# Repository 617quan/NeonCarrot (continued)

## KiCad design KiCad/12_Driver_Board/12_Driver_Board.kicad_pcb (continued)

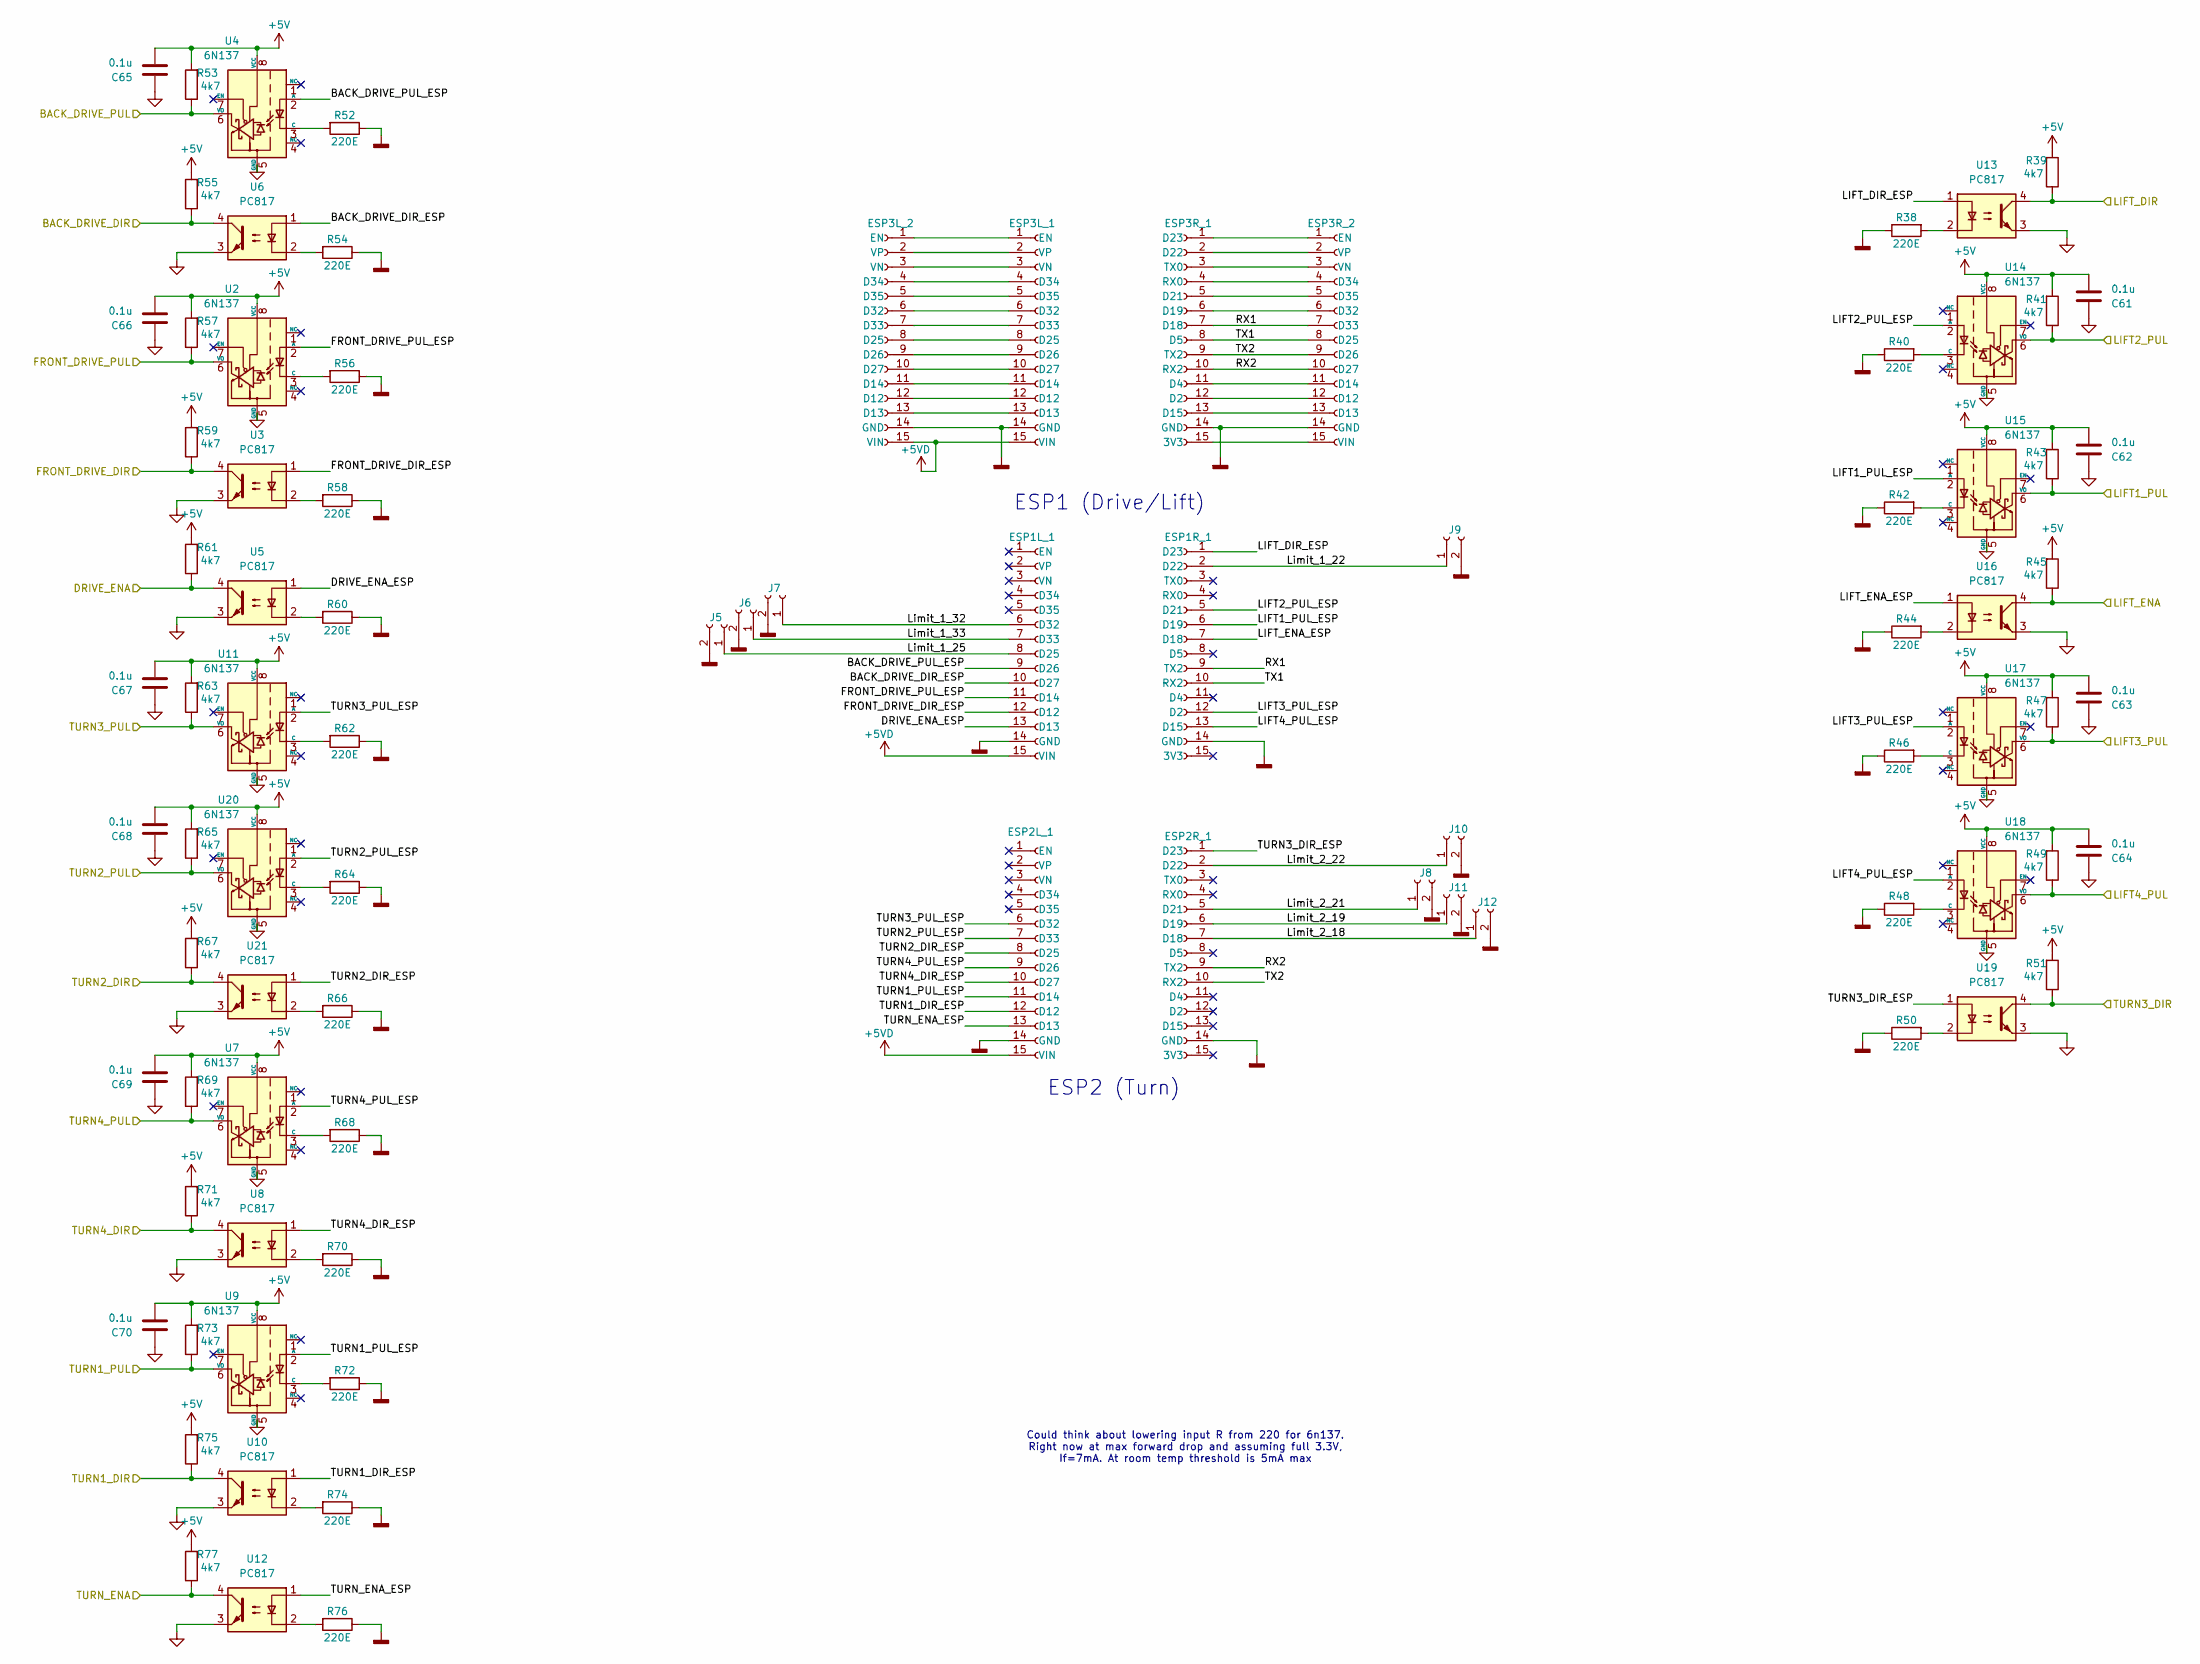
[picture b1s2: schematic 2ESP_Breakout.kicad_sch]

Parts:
C61, C62, C63, C64, C65, C66, C67, C68, C69, C70: 0.1u; C_0805_2012Metric
ESP1L_1, ESP1R_1, ESP2L_1, ESP2R_1, ESP3L_1, ESP3L_2, ESP3R_1, ESP3R_2: Conn_01x15_Socket; PinSocket_1x15_P2.54mm_Vertical
J5, J6, J7, J8, J9, J10, J11, J12: Conn_01x02_Socket; JST_PH_B2B-PH-K_1x02_P2.00mm_Vertical
R38, R40, R42, R44, R46, R48, R50, R52, R54, R56, R58, R60, R62, R64, R66, R68, R70, R72, R74, R76: 220E; R_0805_2012Metric
R39, R41, R43, R45, R47, R49, R51, R53, R55, R57, R59, R61, R63, R65, R67, R69, R71, R73, R75, R77: 4k7; R_0805_2012Metric
U2, U4, U7, U9, U11, U14, U15, U17, U18, U20: 6N137; DIP762W60P254L968H450Q8N
U3, U5, U6, U8, U10, U12, U13, U16, U19, U21: PC817; DIP-4_W7.62mm

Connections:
+5V: C61.1, C62.1, C63.1, C64.1, C65.1, C66.1, C67.1, C68.1, C69.1, C70.1, R39.2, R41.2, R43.2, R45.2, R47.2, R49.2, R51.2, R53.2, R55.2, R57.2, R59.2, R61.2, R63.2, R65.2, R67.2, R69.2, R71.2, R73.2, R75.2, R77.2, U2.8 (VCC), U4.8 (VCC), U7.8 (VCC), U9.8 (VCC), U11.8 (VCC), U14.8 (VCC), U15.8 (VCC), U17.8 (VCC), U18.8 (VCC), U20.8 (VCC); also elsewhere on the board
+5VD: ESP1L_1.15 (VIN), ESP2L_1.15 (VIN), ESP3L_1.15 (VIN), ESP3L_2.15 (VIN)
/BACK_DRIVE_DIR: R55.1, U6.4; also elsewhere on the board
/BACK_DRIVE_PUL: R53.1, U4.6 (VO); also elsewhere on the board
/DRIVE_ENA: R61.1, U5.4; also elsewhere on the board
/ESPs/BACK_DRIVE_DIR_ESP: ESP1L_1.10 (D27), U6.1
/ESPs/BACK_DRIVE_PUL_ESP: ESP1L_1.9 (D26), U4.2 (A)
/ESPs/DRIVE_ENA_ESP: ESP1L_1.13 (D13), U5.1
/ESPs/FRONT_DRIVE_DIR_ESP: ESP1L_1.12 (D12), U3.1
/ESPs/FRONT_DRIVE_PUL_ESP: ESP1L_1.11 (D14), U2.2 (A)
/ESPs/LIFT1_PUL_ESP: ESP1R_1.6 (D19), U15.2 (A)
/ESPs/LIFT2_PUL_ESP: ESP1R_1.5 (D21), U14.2 (A)
/ESPs/LIFT3_PUL_ESP: ESP1R_1.12 (D2), U17.2 (A)
/ESPs/LIFT4_PUL_ESP: ESP1R_1.13 (D15), U18.2 (A)
/ESPs/LIFT_DIR_ESP: ESP1R_1.1 (D23), U13.1
/ESPs/LIFT_ENA_ESP: ESP1R_1.7 (D18), U16.1
/ESPs/Limit_1_22: ESP1R_1.2 (D22), J9.1
/ESPs/Limit_1_25: ESP1L_1.8 (D25), J5.1
/ESPs/Limit_1_32: ESP1L_1.6 (D32), J7.1
/ESPs/Limit_1_33: ESP1L_1.7 (D33), J6.1
/ESPs/Limit_2_18: ESP2R_1.7 (D18), J12.1
/ESPs/Limit_2_19: ESP2R_1.6 (D19), J11.1
/ESPs/Limit_2_21: ESP2R_1.5 (D21), J8.1
/ESPs/Limit_2_22: ESP2R_1.2 (D22), J10.1
/ESPs/RX1: ESP1R_1.9 (TX2), ESP3R_1.7 (D18), ESP3R_2.7 (D33)
/ESPs/RX2: ESP2R_1.9 (TX2), ESP3R_1.10 (RX2), ESP3R_2.10 (D27)
/ESPs/TURN1_DIR_ESP: ESP2L_1.12 (D12), U10.1
/ESPs/TURN1_PUL_ESP: ESP2L_1.11 (D14), U9.2 (A)
/ESPs/TURN2_DIR_ESP: ESP2L_1.8 (D25), U21.1
/ESPs/TURN2_PUL_ESP: ESP2L_1.7 (D33), U20.2 (A)
/ESPs/TURN3_DIR_ESP: ESP2R_1.1 (D23), U19.1
/ESPs/TURN3_PUL_ESP: ESP2L_1.6 (D32), U11.2 (A)
/ESPs/TURN4_DIR_ESP: ESP2L_1.10 (D27), U8.1
/ESPs/TURN4_PUL_ESP: ESP2L_1.9 (D26), U7.2 (A)
/ESPs/TURN_ENA_ESP: ESP2L_1.13 (D13), U12.1
/ESPs/TX1: ESP1R_1.10 (RX2), ESP3R_1.8 (D5), ESP3R_2.8 (D25)
/ESPs/TX2: ESP2R_1.10 (RX2), ESP3R_1.9 (TX2), ESP3R_2.9 (D26)
/FRONT_DRIVE_DIR: R59.1, U3.4; also elsewhere on the board
/FRONT_DRIVE_PUL: R57.1, U2.6 (VO); also elsewhere on the board
/LIFT1_PUL: R43.1, U15.6 (VO); also elsewhere on the board
/LIFT2_PUL: R41.1, U14.6 (VO); also elsewhere on the board
/LIFT3_PUL: R47.1, U17.6 (VO); also elsewhere on the board
/LIFT4_PUL: R49.1, U18.6 (VO); also elsewhere on the board
/LIFT_DIR: R39.1, U13.4; also elsewhere on the board
/LIFT_ENA: R45.1, U16.4; also elsewhere on the board
/TURN1_DIR: R75.1, U10.4; also elsewhere on the board
/TURN1_PUL: R73.1, U9.6 (VO); also elsewhere on the board
/TURN2_DIR: R67.1, U21.4; also elsewhere on the board
/TURN2_PUL: R65.1, U20.6 (VO); also elsewhere on the board
/TURN3_DIR: R51.1, U19.4; also elsewhere on the board
/TURN3_PUL: R63.1, U11.6 (VO); also elsewhere on the board
/TURN4_DIR: R71.1, U8.4; also elsewhere on the board
/TURN4_PUL: R69.1, U7.6 (VO); also elsewhere on the board
/TURN_ENA: R77.1, U12.4; also elsewhere on the board
GND: C61.2, C62.2, C63.2, C64.2, C65.2, C66.2, C67.2, C68.2, C69.2, C70.2, U2.5 (GND), U3.3, U4.5 (GND), U5.3, U6.3, U7.5 (GND), U8.3, U9.5 (GND), U10.3, U11.5 (GND), U12.3, U13.3, U14.5 (GND), U15.5 (GND), U16.3, U17.5 (GND), U18.5 (GND), U19.3, U20.5 (GND), U21.3; also elsewhere on the board
GNDD: ESP1L_1.14 (GND), ESP1R_1.14 (GND), ESP2L_1.14 (GND), ESP2R_1.14 (GND), ESP3L_1.14 (GND), ESP3L_2.14 (GND), ESP3R_1.14 (GND), ESP3R_2.14 (GND), J5.2, J6.2, J7.2, J8.2, J9.2, J10.2, J11.2, J12.2, R38.1, R40.1, R42.1, R44.1, R46.1, R48.1, R50.1, R52.1, R54.1, R56.1, R58.1, R60.1, R62.1, R64.1, R66.1, R68.1, R70.1, R72.1, R74.1, R76.1
unnamed: ESP3L_1.12 (D12), ESP3L_2.12 (D12)
unnamed: ESP3L_1.13 (D13), ESP3L_2.13 (D13)
unnamed: ESP3L_1.11 (D14), ESP3L_2.11 (D14)
unnamed: ESP3L_1.8 (D25), ESP3L_2.8 (D25)
unnamed: ESP3L_1.9 (D26), ESP3L_2.9 (D26)
unnamed: ESP3L_1.10 (D27), ESP3L_2.10 (D27)
unnamed: ESP3L_1.6 (D32), ESP3L_2.6 (D32)
unnamed: ESP3L_1.7 (D33), ESP3L_2.7 (D33)
unnamed: ESP3L_1.4 (D34), ESP3L_2.4 (D34)
unnamed: ESP3L_1.5 (D35), ESP3L_2.5 (D35)
unnamed: ESP3L_1.1 (EN), ESP3L_2.1 (EN)
unnamed: ESP3L_1.3 (VN), ESP3L_2.3 (VN)
unnamed: ESP3L_1.2 (VP), ESP3L_2.2 (VP)
unnamed: ESP3R_1.15 (3V3), ESP3R_2.15 (VIN)
unnamed: ESP3R_1.12 (D2), ESP3R_2.12 (D12)
unnamed: ESP3R_1.11 (D4), ESP3R_2.11 (D14)
unnamed: ESP3R_1.13 (D15), ESP3R_2.13 (D13)
unnamed: ESP3R_1.6 (D19), ESP3R_2.6 (D32)
unnamed: ESP3R_1.5 (D21), ESP3R_2.5 (D35)
unnamed: ESP3R_1.2 (D22), ESP3R_2.2 (VP)
unnamed: ESP3R_1.1 (D23), ESP3R_2.1 (EN)
unnamed: ESP3R_1.4 (RX0), ESP3R_2.4 (D34)
unnamed: ESP3R_1.3 (TX0), ESP3R_2.3 (VN)
unnamed: R38.2, U13.2
unnamed: R44.2, U16.2
unnamed: R50.2, U19.2
unnamed: R54.2, U6.2
unnamed: R58.2, U3.2
unnamed: R60.2, U5.2
unnamed: R66.2, U21.2
unnamed: R70.2, U8.2
unnamed: R74.2, U10.2
unnamed: R76.2, U12.2
unnamed: R56.2, U2.3 (C)
unnamed: R52.2, U4.3 (C)
unnamed: R68.2, U7.3 (C)
unnamed: R72.2, U9.3 (C)
unnamed: R62.2, U11.3 (C)
unnamed: R40.2, U14.3 (C)
unnamed: R42.2, U15.3 (C)
unnamed: R46.2, U17.3 (C)
unnamed: R48.2, U18.3 (C)
unnamed: R64.2, U20.3 (C)

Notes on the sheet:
ESP2 (Turn)
Could think about lowering input R from 220 for 6n137. Right now at max forward drop and assuming full 3.3V, If=7mA. At room temp threshold is 5mA max
ESP1 (Drive/Lift)

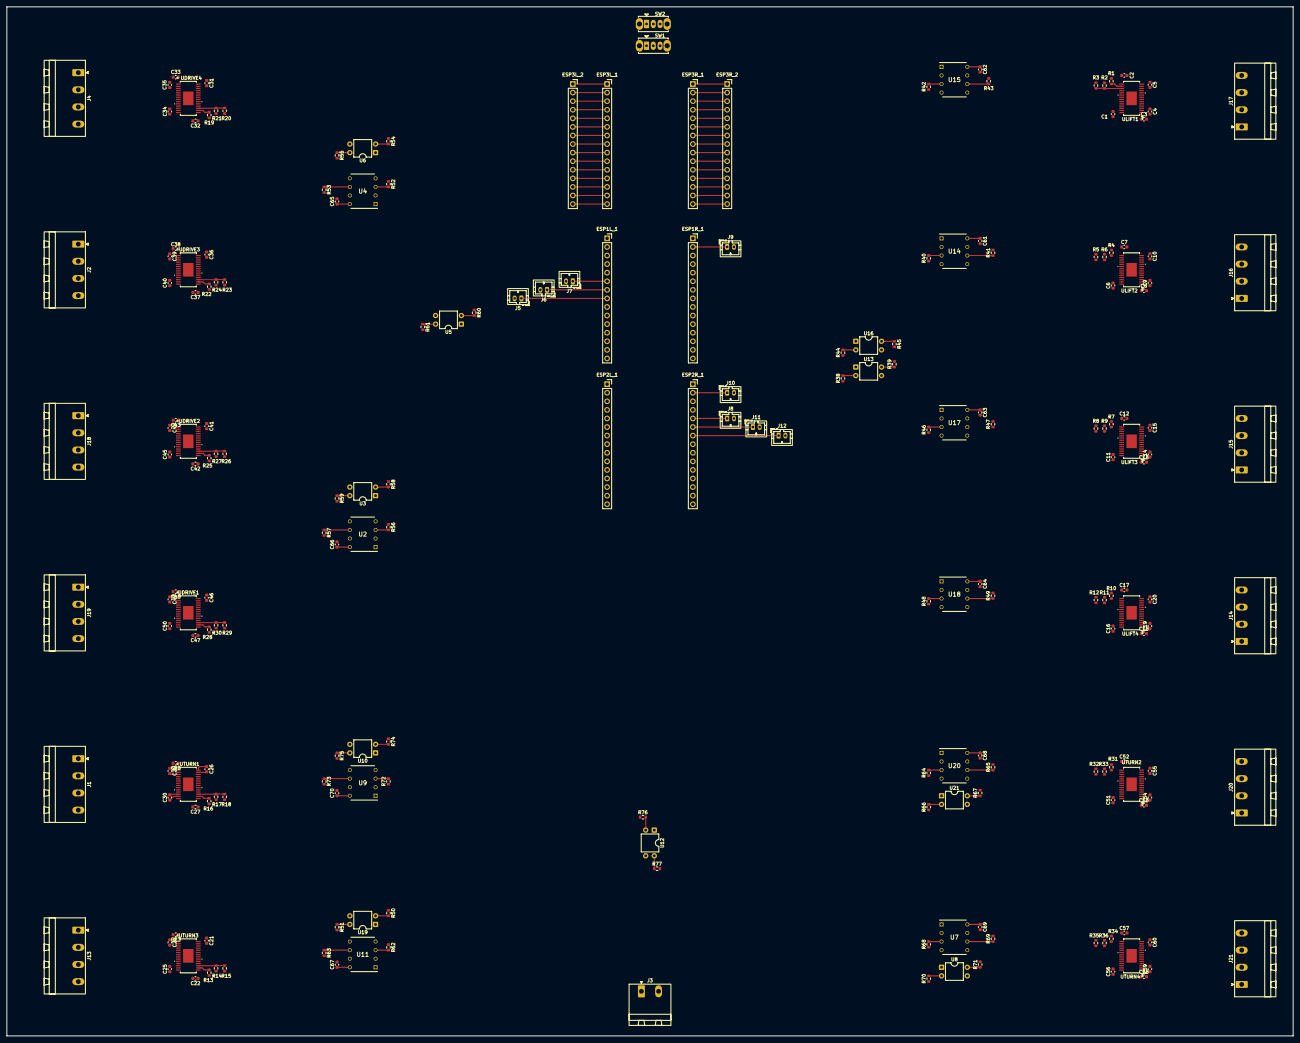
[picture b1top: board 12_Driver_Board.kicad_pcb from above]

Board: 4 copper layers, 381.0 x 304.8 mm, 209 parts (0 on the bottom side), 222 nets.

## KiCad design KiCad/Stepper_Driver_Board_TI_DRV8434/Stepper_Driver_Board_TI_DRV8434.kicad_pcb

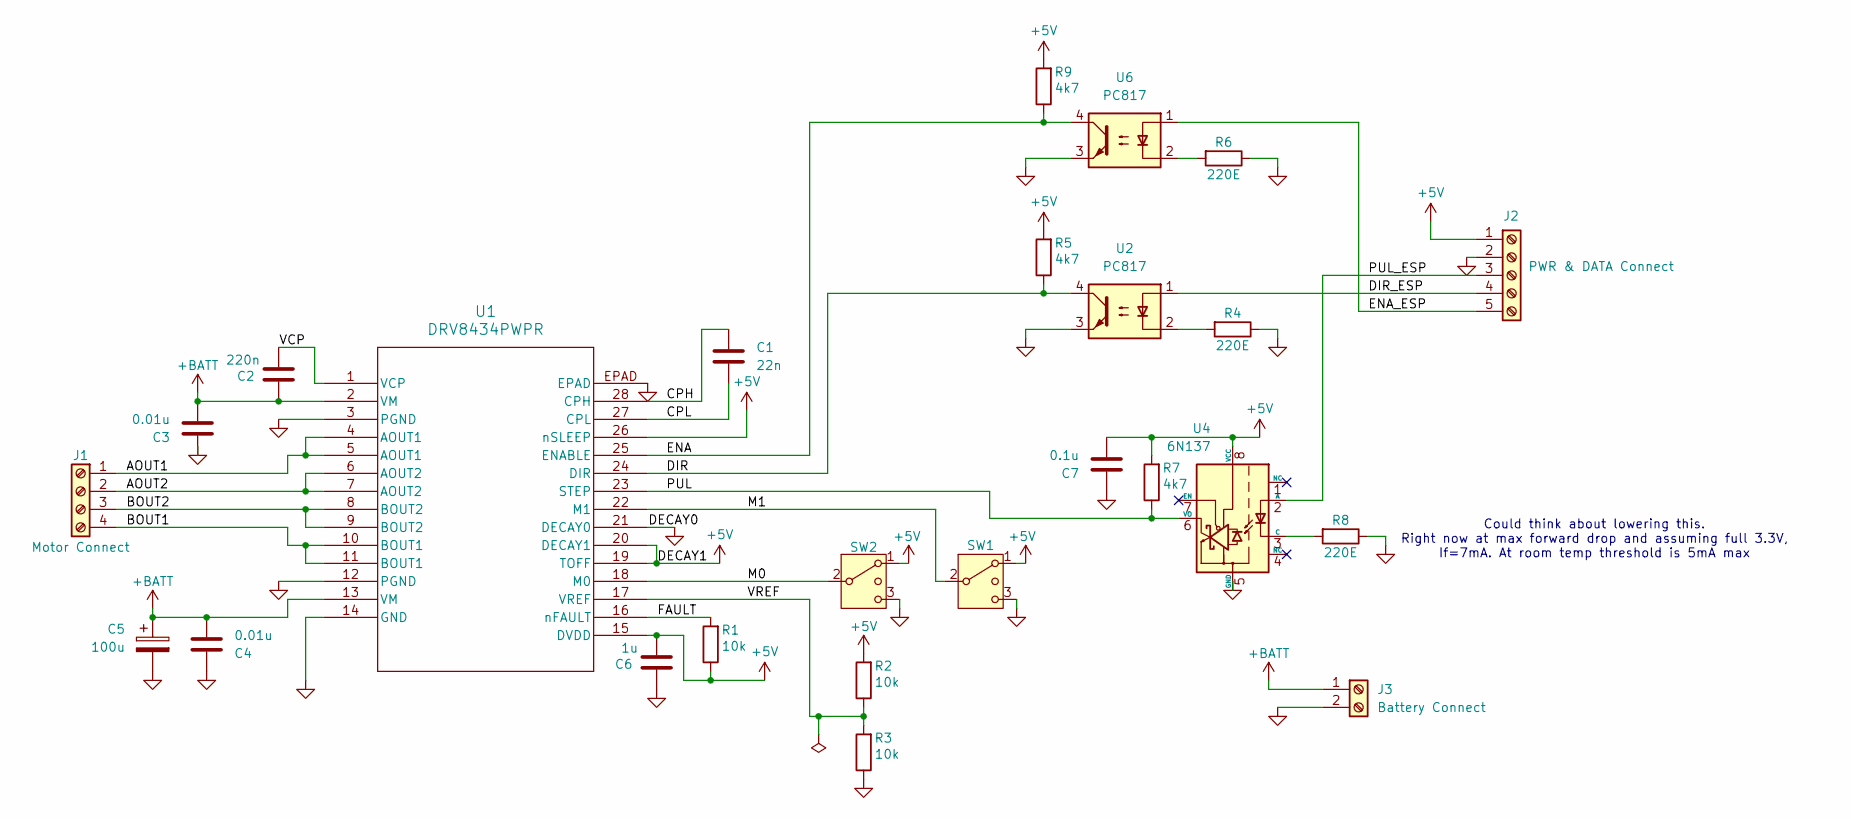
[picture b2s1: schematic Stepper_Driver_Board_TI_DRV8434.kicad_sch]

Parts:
C1: 22n; C_0603_1608Metric_Pad1.08x0.95mm_HandSolder
C2: 220n; C_0603_1608Metric_Pad1.08x0.95mm_HandSolder
C3, C4: 0.01u; C_0603_1608Metric_Pad1.08x0.95mm_HandSolder
C5: 100u; CP_Radial_D8.0mm_P3.50mm
C6: 1u; C_0603_1608Metric_Pad1.08x0.95mm_HandSolder
C7: 0.1u; C_0603_1608Metric_Pad1.08x0.95mm_HandSolder
J1: Motor Connect; PhoenixContact_MSTBA_2,5_4-G-5,08_1x04_P5.08mm_Horizontal
J2: PWR & DATA Connect; PhoenixContact_MSTBA_2,5_5-G-5,08_1x05_P5.08mm_Horizontal
J3: Battery Connect; PhoenixContact_MSTBA_2,5_2-G-5,08_1x02_P5.08mm_Horizontal
R1, R2, R3: 10k; R_0603_1608Metric_Pad0.98x0.95mm_HandSolder
R4, R6, R8: 220E; R_0603_1608Metric_Pad0.98x0.95mm_HandSolder
R5, R7, R9: 4k7; R_0603_1608Metric_Pad0.98x0.95mm_HandSolder
SW1, SW2: SW_SPDT_MSM; SW_Slide_SPDT_Straight_CK_OS102011MS2Q
U1: DRV8434PWPR; TSSOP_34PWPR_TEX
U2, U6: PC817; DIP-4_W7.62mm
U4: 6N137; DIP762W60P254L968H450Q8N

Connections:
+5V: C6.1, C7.1, J2.1, R1.1, R2.2, R5.2, R7.2, R9.2, SW1.1, SW2.1, U1.15 (DVDD), U1.19 (TOFF), U1.20 (DECAY1), U1.26 (nSLEEP), U4.8 (VCC)
+BATT: C2.2, C3.1, C4.1, C5.1, J3.1, U1.2 (VM), U1.13 (VM)
/AOUT1: J1.1, U1.4 (AOUT1), U1.5 (AOUT1)
/AOUT2: J1.2, U1.6 (AOUT2), U1.7 (AOUT2)
/BOUT1: J1.4, U1.10 (BOUT1), U1.11 (BOUT1)
/BOUT2: J1.3, U1.8 (BOUT2), U1.9 (BOUT2)
/CPH: C1.1, U1.28 (CPH)
/CPL: C1.2, U1.27 (CPL)
/DIR: R5.1, U1.24 (DIR), U2.4
/DIR_ESP: J2.4, U2.1
/ENA: R9.1, U1.25 (ENABLE), U6.4
/ENA_ESP: J2.5, U6.1
/FAULT: R1.2, U1.16 (nFAULT)
/M0: SW2.2 (3), U1.18 (M0)
/M1: SW1.2 (3), U1.22 (M1)
/PUL: R7.1, U1.23 (STEP), U4.6 (VO)
/PUL_ESP: J2.3, U4.2 (A)
/VCP: C2.1, U1.1 (VCP)
/VREF: R2.1, R3.2, U1.17 (VREF)
GND: C3.2, C4.2, C5.2, C6.2, C7.2, J2.2, J3.2, R3.1, R4.1, R6.1, R8.1, SW1.3 (4), SW2.3 (4), U1.3 (PGND), U1.12 (PGND), U1.14 (GND), U1.21 (DECAY0), U1.EPAD, U2.3, U4.5 (GND), U6.3
unnamed: R4.2, U2.2
unnamed: R6.2, U6.2
unnamed: R8.2, U4.3 (C)

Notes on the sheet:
Could think about lowering this. Right now at max forward drop and assuming full 3.3V, If=7mA. At room temp threshold is 5mA max

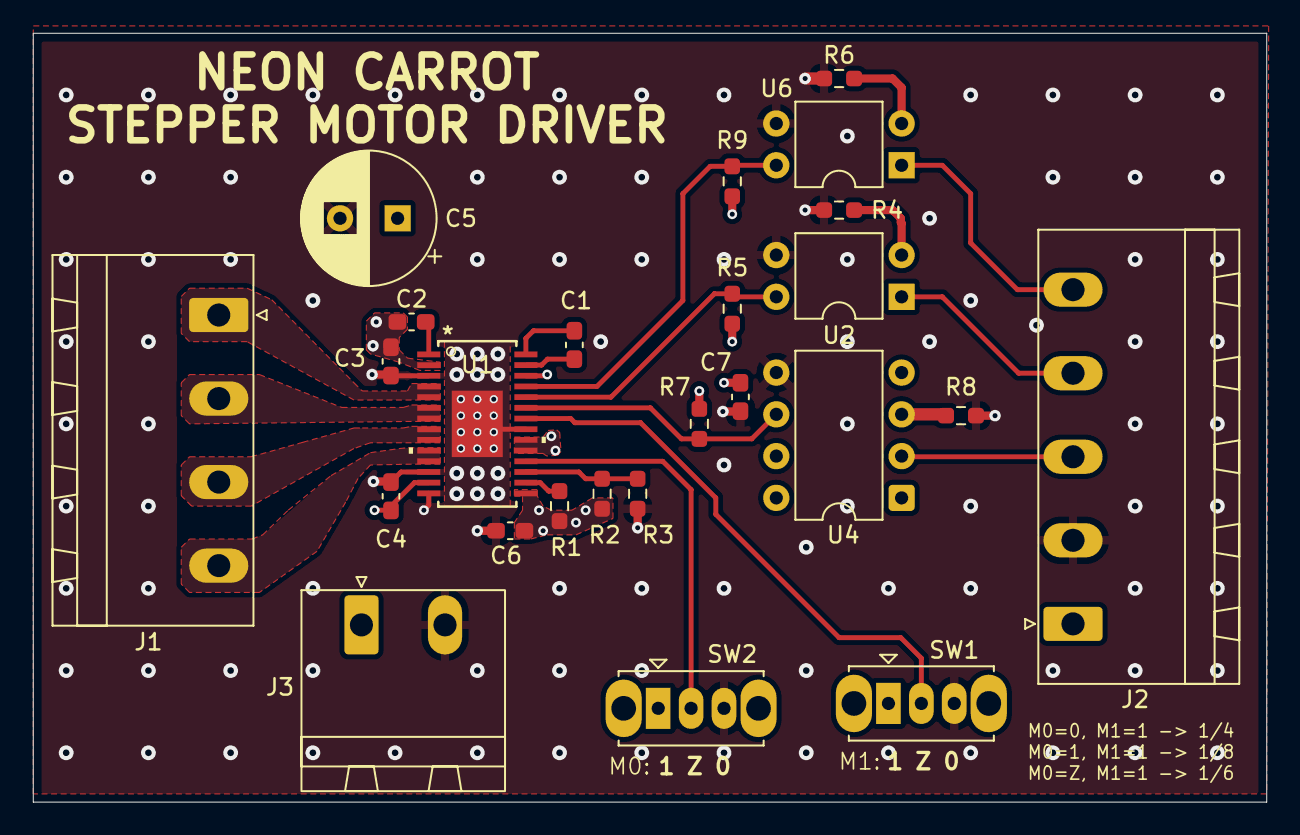
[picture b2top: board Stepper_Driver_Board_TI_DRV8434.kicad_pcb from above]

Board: 4 copper layers, 75.0 x 46.8 mm, 25 parts (0 on the bottom side), 23 nets.

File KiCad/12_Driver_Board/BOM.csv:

"Reference","Value","Datasheet","Footprint","Qty","DNP"
"C1","22n","~","Capacitor_SMD:C_0603_1608Metric_Pad1.08x0.95mm_HandSolder","1",""
"C2","220n","~","Capacitor_SMD:C_0603_1608Metric_Pad1.08x0.95mm_HandSolder","1",""
"C3,C4","0.01u","~","Capacitor_SMD:C_0603_1608Metric_Pad1.08x0.95mm_HandSolder","2",""
"C5","100u","~","","1",""
"C6","1u","~","Capacitor_SMD:C_0603_1608Metric_Pad1.08x0.95mm_HandSolder","1",""
"C7","0.1u","~","Capacitor_SMD:C_0603_1608Metric_Pad1.08x0.95mm_HandSolder","1",""
"J1","Motor Connect","~","Connector_Phoenix_MSTB:PhoenixContact_MSTBA_2,5_4-G-5,08_1x04_P5.08mm_Horizontal","1",""
"J2","PWR & DATA Connect","~","Connector_Phoenix_MSTB:PhoenixContact_MSTBA_2,5_5-G-5,08_1x05_P5.08mm_Horizontal","1",""
"R1,R2,R3","10k","~","Resistor_SMD:R_0603_1608Metric_Pad0.98x0.95mm_HandSolder","3",""
"R4,R6,R8","220E","~","Resistor_SMD:R_0603_1608Metric_Pad0.98x0.95mm_HandSolder","3",""
"R5,R7,R9","4k7","~","Resistor_SMD:R_0603_1608Metric_Pad0.98x0.95mm_HandSolder","3",""
"SW1,SW2","SW_SPDT_MSM","~","Button_Switch_THT:SW_Slide_SPDT_Straight_CK_OS102011MS2Q","2",""
"U1","DRV8434PWPR","https://www.ti.com/lit/gpn/drv8434","TSSOP_34PWPR_TEX","1",""
"U2,U6","PC817","http://www.soselectronic.cz/a_info/resource/d/pc817.pdf","Package_DIP:DIP-4_W7.62mm","2",""
"U4","6N137","https://docs.broadcom.com/docs/AV02-0940EN","Package_DIP:DIP-8_W7.62mm","1",""

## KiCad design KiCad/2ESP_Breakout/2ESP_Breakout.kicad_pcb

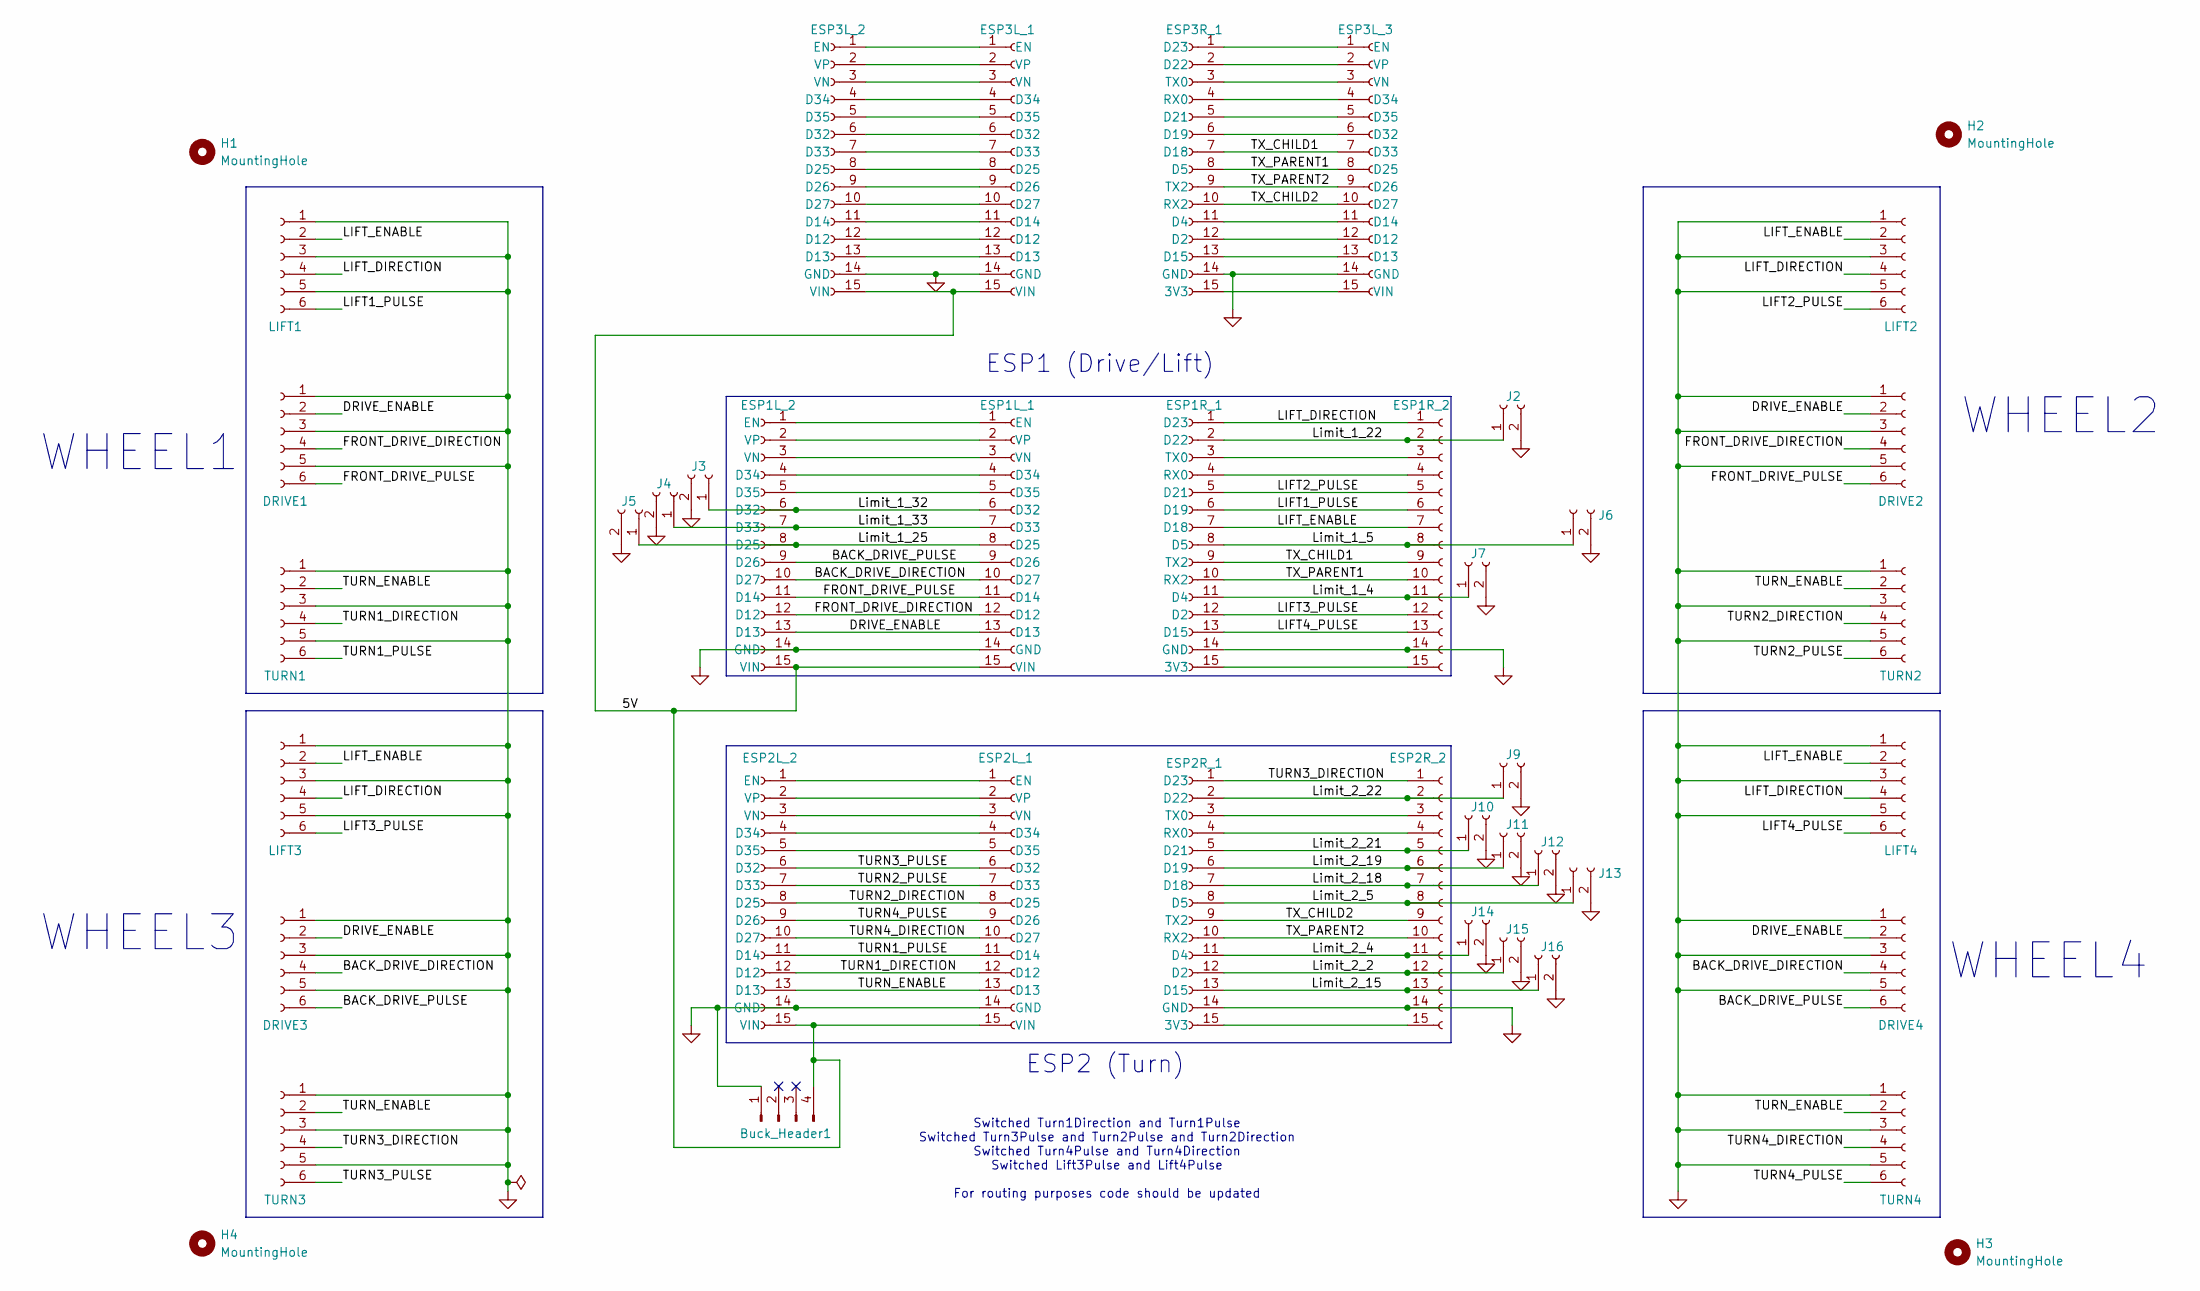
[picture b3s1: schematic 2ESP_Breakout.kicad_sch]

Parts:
Buck_Header1: Conn_01x04_Pin; PinHeader_1x04_P2.54mm_Vertical
DRIVE1, DRIVE2, DRIVE3, DRIVE4: Conn_01x06_Socket; JST_PH_B6B-PH-K_1x06_P2.00mm_Vertical
ESP1L_1, ESP1L_2, ESP1R_1, ESP1R_2, ESP2L_1, ESP2L_2, ESP2R_1, ESP2R_2, ESP3L_1, ESP3L_2, ESP3L_3, ESP3R_1: Conn_01x15_Socket; PinSocket_1x15_P2.54mm_Vertical
H1, H2, H3, H4: MountingHole; MountingHole_3.2mm_M3
J2, J3, J4, J5, J6, J7, J9, J10, J11, J12, J13, J14, J15, J16: Conn_01x02_Socket; JST_PH_B2B-PH-K_1x02_P2.00mm_Vertical
LIFT1, LIFT2, LIFT3, LIFT4: Conn_01x06_Socket; JST_PH_B6B-PH-K_1x06_P2.00mm_Vertical
TURN1, TURN2, TURN3, TURN4: Conn_01x06_Socket; JST_PH_B6B-PH-K_1x06_P2.00mm_Vertical

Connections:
/5V: Buck_Header1.4, ESP1L_1.15 (VIN), ESP1L_2.15 (VIN), ESP2L_1.15 (VIN), ESP2L_2.15 (VIN), ESP3L_1.15 (VIN), ESP3L_2.15 (VIN)
/BACK_DRIVE_DIRECTION: DRIVE3.4, DRIVE4.4, ESP1L_1.10 (D27), ESP1L_2.10 (D27)
/BACK_DRIVE_PULSE: DRIVE3.6, DRIVE4.6, ESP1L_1.9 (D26), ESP1L_2.9 (D26)
/DRIVE_ENABLE: DRIVE1.2, DRIVE2.2, DRIVE3.2, DRIVE4.2, ESP1L_1.13 (D13), ESP1L_2.13 (D13)
/FRONT_DRIVE_DIRECTION: DRIVE1.4, DRIVE2.4, ESP1L_1.12 (D12), ESP1L_2.12 (D12)
/FRONT_DRIVE_PULSE: DRIVE1.6, DRIVE2.6, ESP1L_1.11 (D14), ESP1L_2.11 (D14)
/LIFT1_PULSE: ESP1R_1.6 (D19), ESP1R_2.6 (D19), LIFT1.6
/LIFT2_PULSE: ESP1R_1.5 (D21), ESP1R_2.5 (D21), LIFT2.6
/LIFT3_PULSE: ESP1R_1.12 (D2), ESP1R_2.12 (D2), LIFT3.6
/LIFT4_PULSE: ESP1R_1.13 (D15), ESP1R_2.13 (D15), LIFT4.6
/LIFT_DIRECTION: ESP1R_1.1 (D23), ESP1R_2.1 (D23), LIFT1.4, LIFT2.4, LIFT3.4, LIFT4.4
/LIFT_ENABLE: ESP1R_1.7 (D18), ESP1R_2.7 (D18), LIFT1.2, LIFT2.2, LIFT3.2, LIFT4.2
/Limit_1_4: ESP1R_1.11 (D4), ESP1R_2.11 (D4), J7.1
/Limit_1_5: ESP1R_1.8 (D5), ESP1R_2.8 (D5), J6.1
/Limit_1_22: ESP1R_1.2 (D22), ESP1R_2.2 (D22), J2.1
/Limit_1_25: ESP1L_1.8 (D25), ESP1L_2.8 (D25), J5.1
/Limit_1_32: ESP1L_1.6 (D32), ESP1L_2.6 (D32), J3.1
/Limit_1_33: ESP1L_1.7 (D33), ESP1L_2.7 (D33), J4.1
/Limit_2_2: ESP2R_1.12 (D2), ESP2R_2.12 (D2), J15.1
/Limit_2_4: ESP2R_1.11 (D4), ESP2R_2.11 (D4), J14.1
/Limit_2_5: ESP2R_1.8 (D5), ESP2R_2.8 (D5), J13.1
/Limit_2_15: ESP2R_1.13 (D15), ESP2R_2.13 (D15), J16.1
/Limit_2_18: ESP2R_1.7 (D18), ESP2R_2.7 (D18), J12.1
/Limit_2_19: ESP2R_1.6 (D19), ESP2R_2.6 (D19), J11.1
/Limit_2_21: ESP2R_1.5 (D21), ESP2R_2.5 (D21), J10.1
/Limit_2_22: ESP2R_1.2 (D22), ESP2R_2.2 (D22), J9.1
/TURN1_DIRECTION: ESP2L_1.12 (D12), ESP2L_2.12 (D12), TURN1.4
/TURN1_PULSE: ESP2L_1.11 (D14), ESP2L_2.11 (D14), TURN1.6
/TURN2_DIRECTION: ESP2L_1.8 (D25), ESP2L_2.8 (D25), TURN2.4
/TURN2_PULSE: ESP2L_1.7 (D33), ESP2L_2.7 (D33), TURN2.6
/TURN3_DIRECTION: ESP2R_1.1 (D23), ESP2R_2.1 (D23), TURN3.4
/TURN3_PULSE: ESP2L_1.6 (D32), ESP2L_2.6 (D32), TURN3.6
/TURN4_DIRECTION: ESP2L_1.10 (D27), ESP2L_2.10 (D27), TURN4.4
/TURN4_PULSE: ESP2L_1.9 (D26), ESP2L_2.9 (D26), TURN4.6
/TURN_ENABLE: ESP2L_1.13 (D13), ESP2L_2.13 (D13), TURN1.2, TURN2.2, TURN3.2, TURN4.2
/TX_CHILD1: ESP1R_1.9 (TX2), ESP1R_2.9 (TX2), ESP3L_3.7 (D33), ESP3R_1.7 (D18)
/TX_CHILD2: ESP2R_1.9 (TX2), ESP2R_2.9 (TX2), ESP3L_3.10 (D27), ESP3R_1.10 (RX2)
/TX_PARENT1: ESP1R_1.10 (RX2), ESP1R_2.10 (RX2), ESP3L_3.8 (D25), ESP3R_1.8 (D5)
/TX_PARENT2: ESP2R_1.10 (RX2), ESP2R_2.10 (RX2), ESP3L_3.9 (D26), ESP3R_1.9 (TX2)
GND: Buck_Header1.1, DRIVE1.1, DRIVE1.3, DRIVE1.5, DRIVE2.1, DRIVE2.3, DRIVE2.5, DRIVE3.1, DRIVE3.3, DRIVE3.5, DRIVE4.1, DRIVE4.3, DRIVE4.5, ESP1L_1.14 (GND), ESP1L_2.14 (GND), ESP1R_1.14 (GND), ESP1R_2.14 (GND), ESP2L_1.14 (GND), ESP2L_2.14 (GND), ESP2R_1.14 (GND), ESP2R_2.14 (GND), ESP3L_1.14 (GND), ESP3L_2.14 (GND), ESP3L_3.14 (GND), ESP3R_1.14 (GND), J2.2, J3.2, J4.2, J5.2, J6.2, J7.2, J9.2, J10.2, J11.2, J12.2, J13.2, J14.2, J15.2, J16.2, LIFT1.1, LIFT1.3, LIFT1.5, LIFT2.1, LIFT2.3, LIFT2.5, LIFT3.1, LIFT3.3, LIFT3.5, LIFT4.1, LIFT4.3, LIFT4.5, TURN1.1, TURN1.3, TURN1.5, TURN2.1, TURN2.3, TURN2.5, TURN3.1, TURN3.3, TURN3.5, TURN4.1, TURN4.3, TURN4.5
unnamed: ESP1L_1.4 (D34), ESP1L_2.4 (D34)
unnamed: ESP1L_1.5 (D35), ESP1L_2.5 (D35)
unnamed: ESP1L_1.1 (EN), ESP1L_2.1 (EN)
unnamed: ESP1L_1.3 (VN), ESP1L_2.3 (VN)
unnamed: ESP1L_1.2 (VP), ESP1L_2.2 (VP)
unnamed: ESP1R_1.15 (3V3), ESP1R_2.15 (3V3)
unnamed: ESP1R_1.4 (RX0), ESP1R_2.4 (RX0)
unnamed: ESP1R_1.3 (TX0), ESP1R_2.3 (TX0)
unnamed: ESP2L_1.4 (D34), ESP2L_2.4 (D34)
unnamed: ESP2L_1.5 (D35), ESP2L_2.5 (D35)
unnamed: ESP2L_1.1 (EN), ESP2L_2.1 (EN)
unnamed: ESP2L_1.3 (VN), ESP2L_2.3 (VN)
unnamed: ESP2L_1.2 (VP), ESP2L_2.2 (VP)
unnamed: ESP2R_1.15 (3V3), ESP2R_2.15 (3V3)
unnamed: ESP2R_1.4 (RX0), ESP2R_2.4 (RX0)
unnamed: ESP2R_1.3 (TX0), ESP2R_2.3 (TX0)
unnamed: ESP3L_1.12 (D12), ESP3L_2.12 (D12)
unnamed: ESP3L_1.13 (D13), ESP3L_2.13 (D13)
unnamed: ESP3L_1.11 (D14), ESP3L_2.11 (D14)
unnamed: ESP3L_1.8 (D25), ESP3L_2.8 (D25)
unnamed: ESP3L_1.9 (D26), ESP3L_2.9 (D26)
unnamed: ESP3L_1.10 (D27), ESP3L_2.10 (D27)
unnamed: ESP3L_1.6 (D32), ESP3L_2.6 (D32)
unnamed: ESP3L_1.7 (D33), ESP3L_2.7 (D33)
unnamed: ESP3L_1.4 (D34), ESP3L_2.4 (D34)
unnamed: ESP3L_1.5 (D35), ESP3L_2.5 (D35)
unnamed: ESP3L_1.1 (EN), ESP3L_2.1 (EN)
unnamed: ESP3L_1.3 (VN), ESP3L_2.3 (VN)
unnamed: ESP3L_1.2 (VP), ESP3L_2.2 (VP)
unnamed: ESP3L_3.12 (D12), ESP3R_1.12 (D2)
unnamed: ESP3L_3.13 (D13), ESP3R_1.13 (D15)
unnamed: ESP3L_3.11 (D14), ESP3R_1.11 (D4)
unnamed: ESP3L_3.6 (D32), ESP3R_1.6 (D19)
unnamed: ESP3L_3.4 (D34), ESP3R_1.4 (RX0)
unnamed: ESP3L_3.5 (D35), ESP3R_1.5 (D21)
unnamed: ESP3L_3.1 (EN), ESP3R_1.1 (D23)
unnamed: ESP3L_3.15 (VIN), ESP3R_1.15 (3V3)
unnamed: ESP3L_3.3 (VN), ESP3R_1.3 (TX0)
unnamed: ESP3L_3.2 (VP), ESP3R_1.2 (D22)

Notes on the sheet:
ESP2 (Turn)
WHEEL3
Switched Turn1Direction and Turn1Pulse Switched Turn3Pulse and Turn2Pulse and Turn2Direction Switched Turn4Pulse and Turn4Direction Switched Lift3Pulse and Lift4Pulse For routing purposes code should be updated
WHEEL2
ESP1 (Drive/Lift)
WHEEL4
WHEEL1

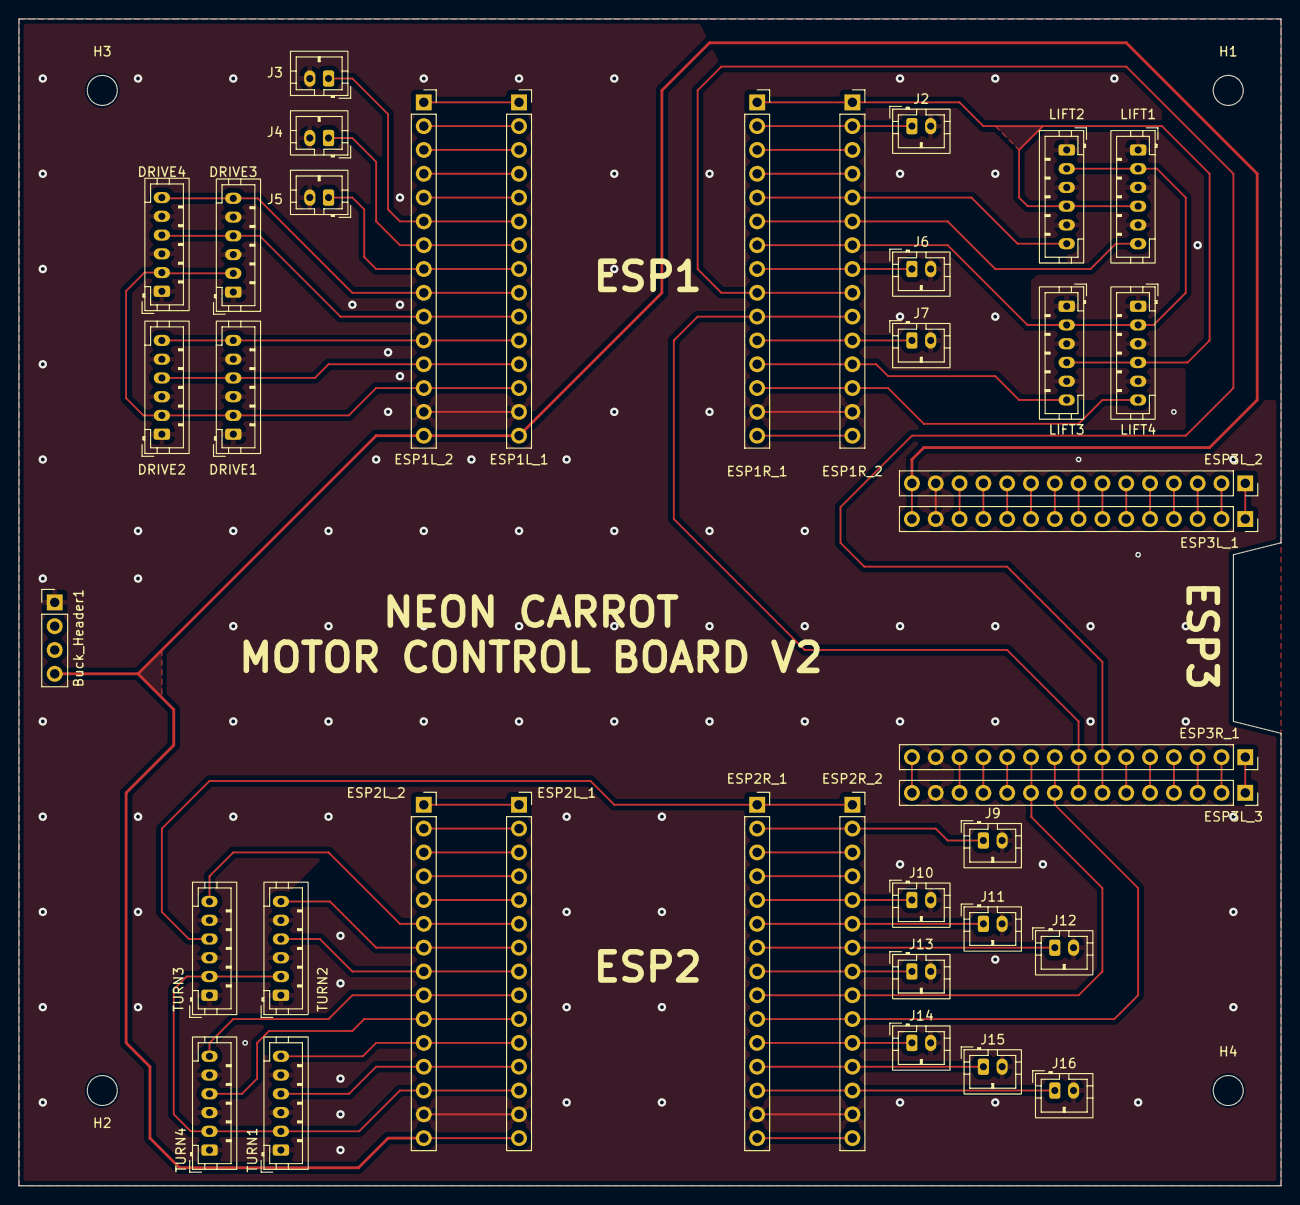
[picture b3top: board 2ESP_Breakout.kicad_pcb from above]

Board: 2 copper layers, 134.6 x 124.5 mm, 43 parts (0 on the bottom side), 79 nets.
